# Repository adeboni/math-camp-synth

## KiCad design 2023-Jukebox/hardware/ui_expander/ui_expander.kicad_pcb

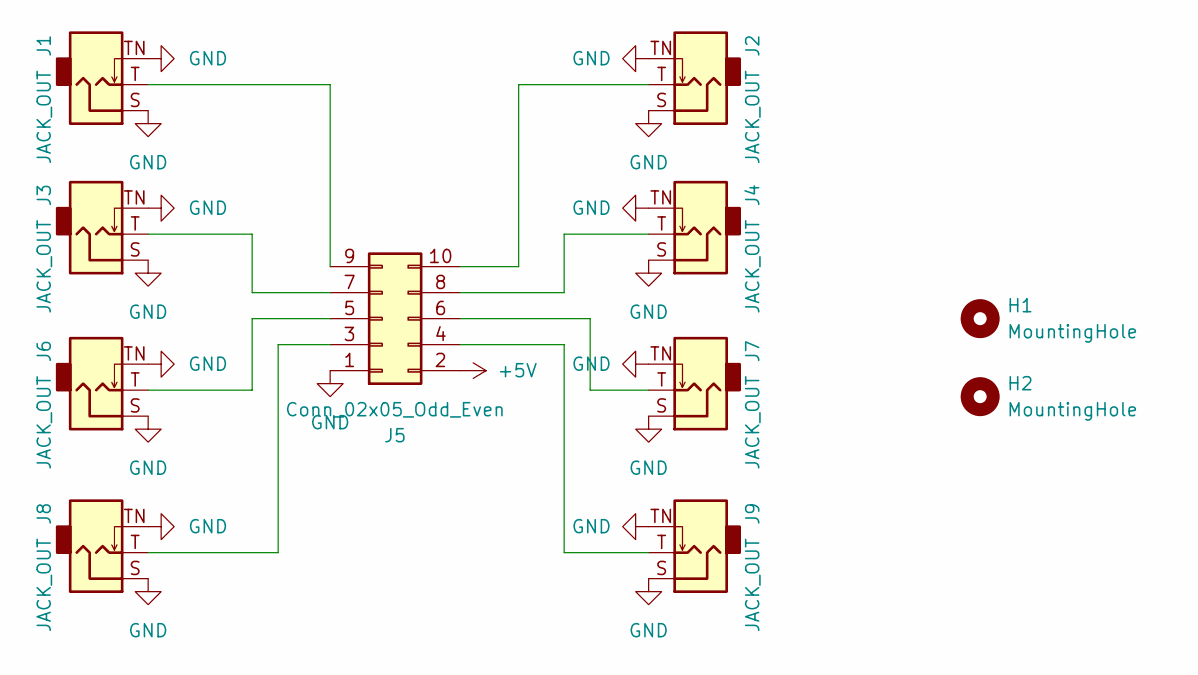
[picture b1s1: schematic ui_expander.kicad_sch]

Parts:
H1, H2: MountingHole; MountingHole_2.2mm_M2
J1, J2, J3, J4, J6, J7, J8, J9: JACK_OUT; Jack_3.5mm_QingPu_WQP-PJ398SM_Vertical_CircularHoles
J5: Conn_02x05_Odd_Even; IDC-Header_2x05_P2.54mm_Vertical

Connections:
+5V: J5.2
GND: J1.S, J1.TN, J2.S, J2.TN, J3.S, J3.TN, J4.S, J4.TN, J5.1, J6.S, J6.TN, J7.S, J7.TN, J8.S, J8.TN, J9.S, J9.TN
unnamed: J1.T, J5.9
unnamed: J2.T, J5.10
unnamed: J3.T, J5.7
unnamed: J4.T, J5.8
unnamed: J5.3, J8.T
unnamed: J5.4, J9.T
unnamed: J5.5, J6.T
unnamed: J5.6, J7.T

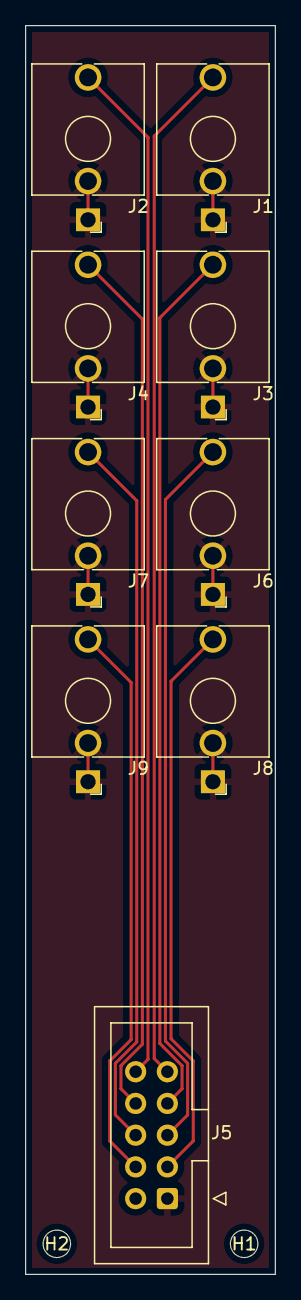
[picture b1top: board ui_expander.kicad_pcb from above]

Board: 2 copper layers, 20.0 x 100.0 mm, 11 parts (0 on the bottom side), 9 nets.

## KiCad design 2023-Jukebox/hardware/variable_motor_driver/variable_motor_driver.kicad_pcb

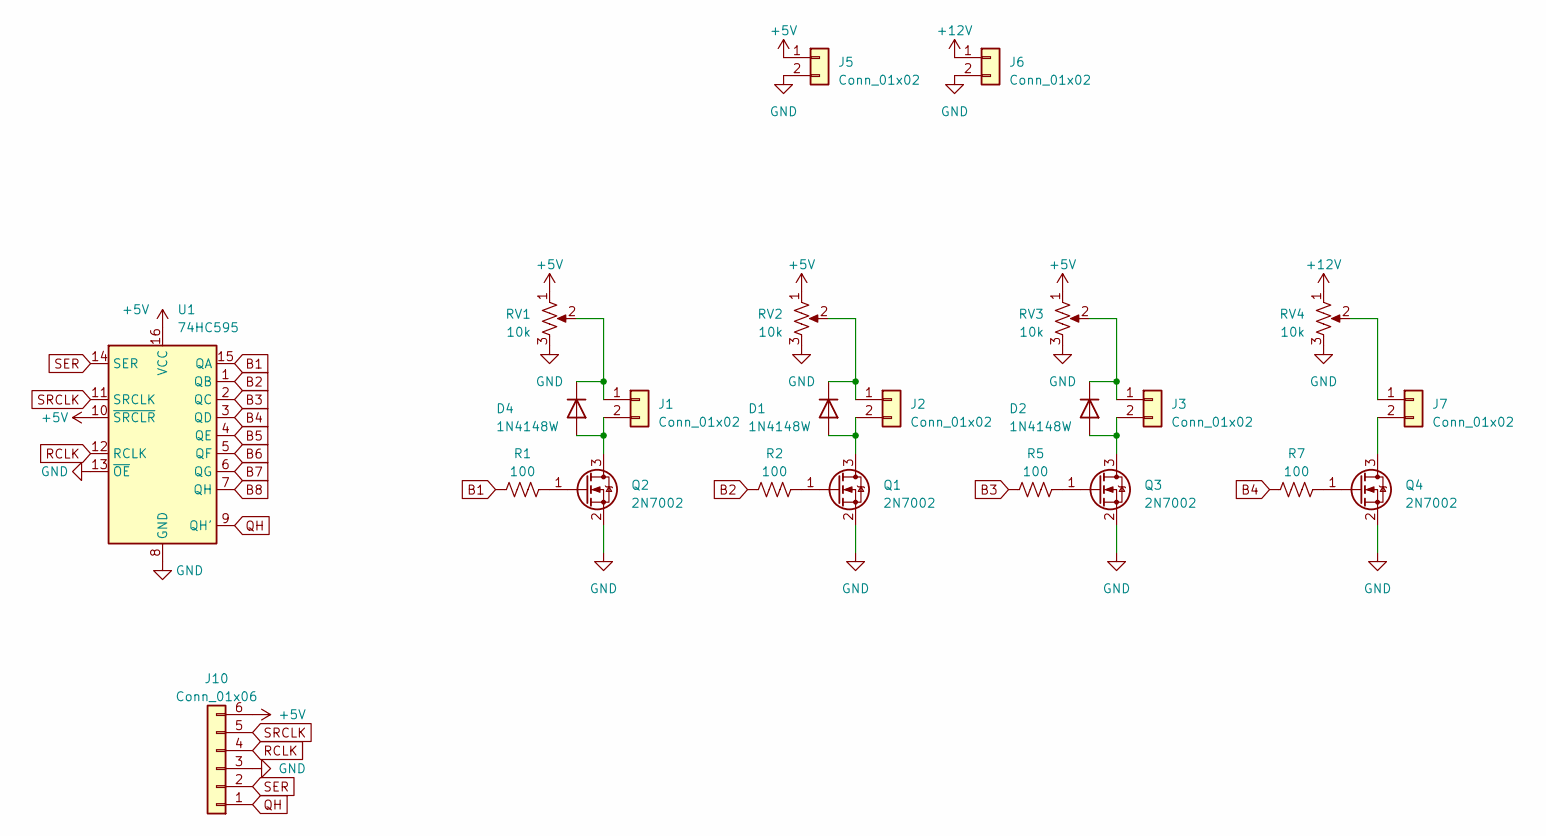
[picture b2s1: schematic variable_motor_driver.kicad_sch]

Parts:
D1, D2, D4: 1N4148W; D_SOD-123
J1, J2, J3, J5, J6, J7: Conn_01x02; JST_XH_B2B-XH-A_1x02_P2.50mm_Vertical
J10: Conn_01x06; PinSocket_1x06_P2.54mm_Vertical
Q1, Q2, Q3, Q4: 2N7002; SOT-23
R1, R2, R5, R7: 100; R_0603_1608Metric
RV1, RV2, RV3, RV4: 10k; Potentiometer_Bourns_3386P_Vertical
U1: 74HC595; SOIC-16_3.9x9.9mm_P1.27mm

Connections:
+5V: J5.1, RV1.1, RV2.1, RV3.1, U1.10 (~SRCLR), U1.16 (VCC); also elsewhere on the board
+12V: J6.1, RV4.1
B1: R1.1, U1.15 (QA)
B2: R2.1, U1.1 (QB)
B3: R5.1, U1.2 (QC)
B4: R7.1, U1.3 (QD)
B5: U1.4 (QE)
B6: U1.5 (QF)
B7: U1.6 (QG)
B8: U1.7 (QH)
GND: J5.2, J6.2, Q1.2 (S), Q2.2 (S), Q3.2 (S), Q4.2 (S), RV1.3, RV2.3, RV3.3, RV4.3, U1.8 (GND), U1.13 (~OE); also elsewhere on the board
unnamed: D1.2 (A), J2.2, Q1.3 (D)
unnamed: D1.1 (K), J2.1, RV2.2
unnamed: D2.2 (A), J3.2, Q3.3 (D)
unnamed: D2.1 (K), J3.1, RV3.2
unnamed: D4.2 (A), J1.2, Q2.3 (D)
unnamed: D4.1 (K), J1.1, RV1.2
unnamed: J7.1, RV4.2
unnamed: J7.2, Q4.3 (D)
unnamed: Q1.1 (G), R2.2
unnamed: Q2.1 (G), R1.2
unnamed: Q3.1 (G), R5.2
unnamed: Q4.1 (G), R7.2
QH: U1.9 (QH'); also elsewhere on the board
RCLK: U1.12 (RCLK); also elsewhere on the board
SER: U1.14 (SER); also elsewhere on the board
SRCLK: U1.11 (SRCLK); also elsewhere on the board

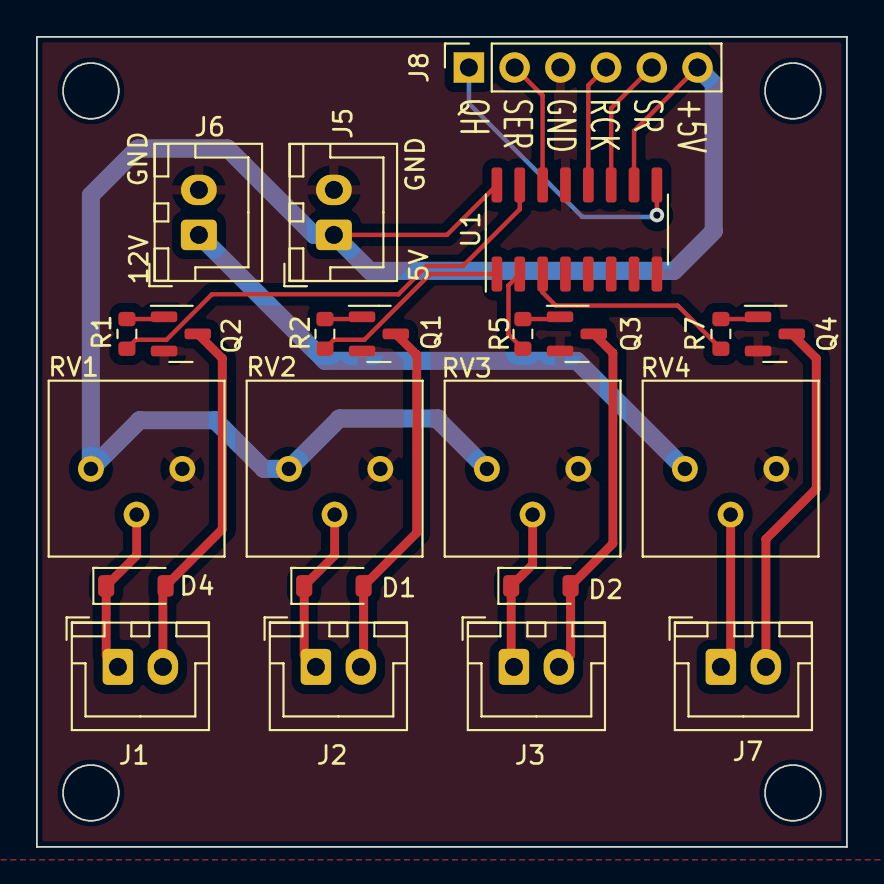
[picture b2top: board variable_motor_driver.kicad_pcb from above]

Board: 2 copper layers, 45.0 x 45.0 mm, 23 parts (0 on the bottom side), 23 nets.

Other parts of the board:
J8: Conn_01x06; PinSocket_1x06_P2.54mm_Vertical

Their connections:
+5V: J8.6; also elsewhere on the board
GND: J8.3; also elsewhere on the board
QH: J8.1; also elsewhere on the board
RCLK: J8.4; also elsewhere on the board
SER: J8.2; also elsewhere on the board
SRCLK: J8.5; also elsewhere on the board

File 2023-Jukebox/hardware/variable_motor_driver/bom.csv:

Comment,Designator,Footprint,LCSC Part Number
74HC595,U1,SOIC-16_3.9x9.9mm_P1.27mm,C5947
100,"R7,R5,R2,R1",R_0603_1608Metric,C22775
2N7002,"Q4,Q3,Q2,Q1",SOT-23,C8545
1N4148W,"D4,D2,D1",D_SOD-123,C81598

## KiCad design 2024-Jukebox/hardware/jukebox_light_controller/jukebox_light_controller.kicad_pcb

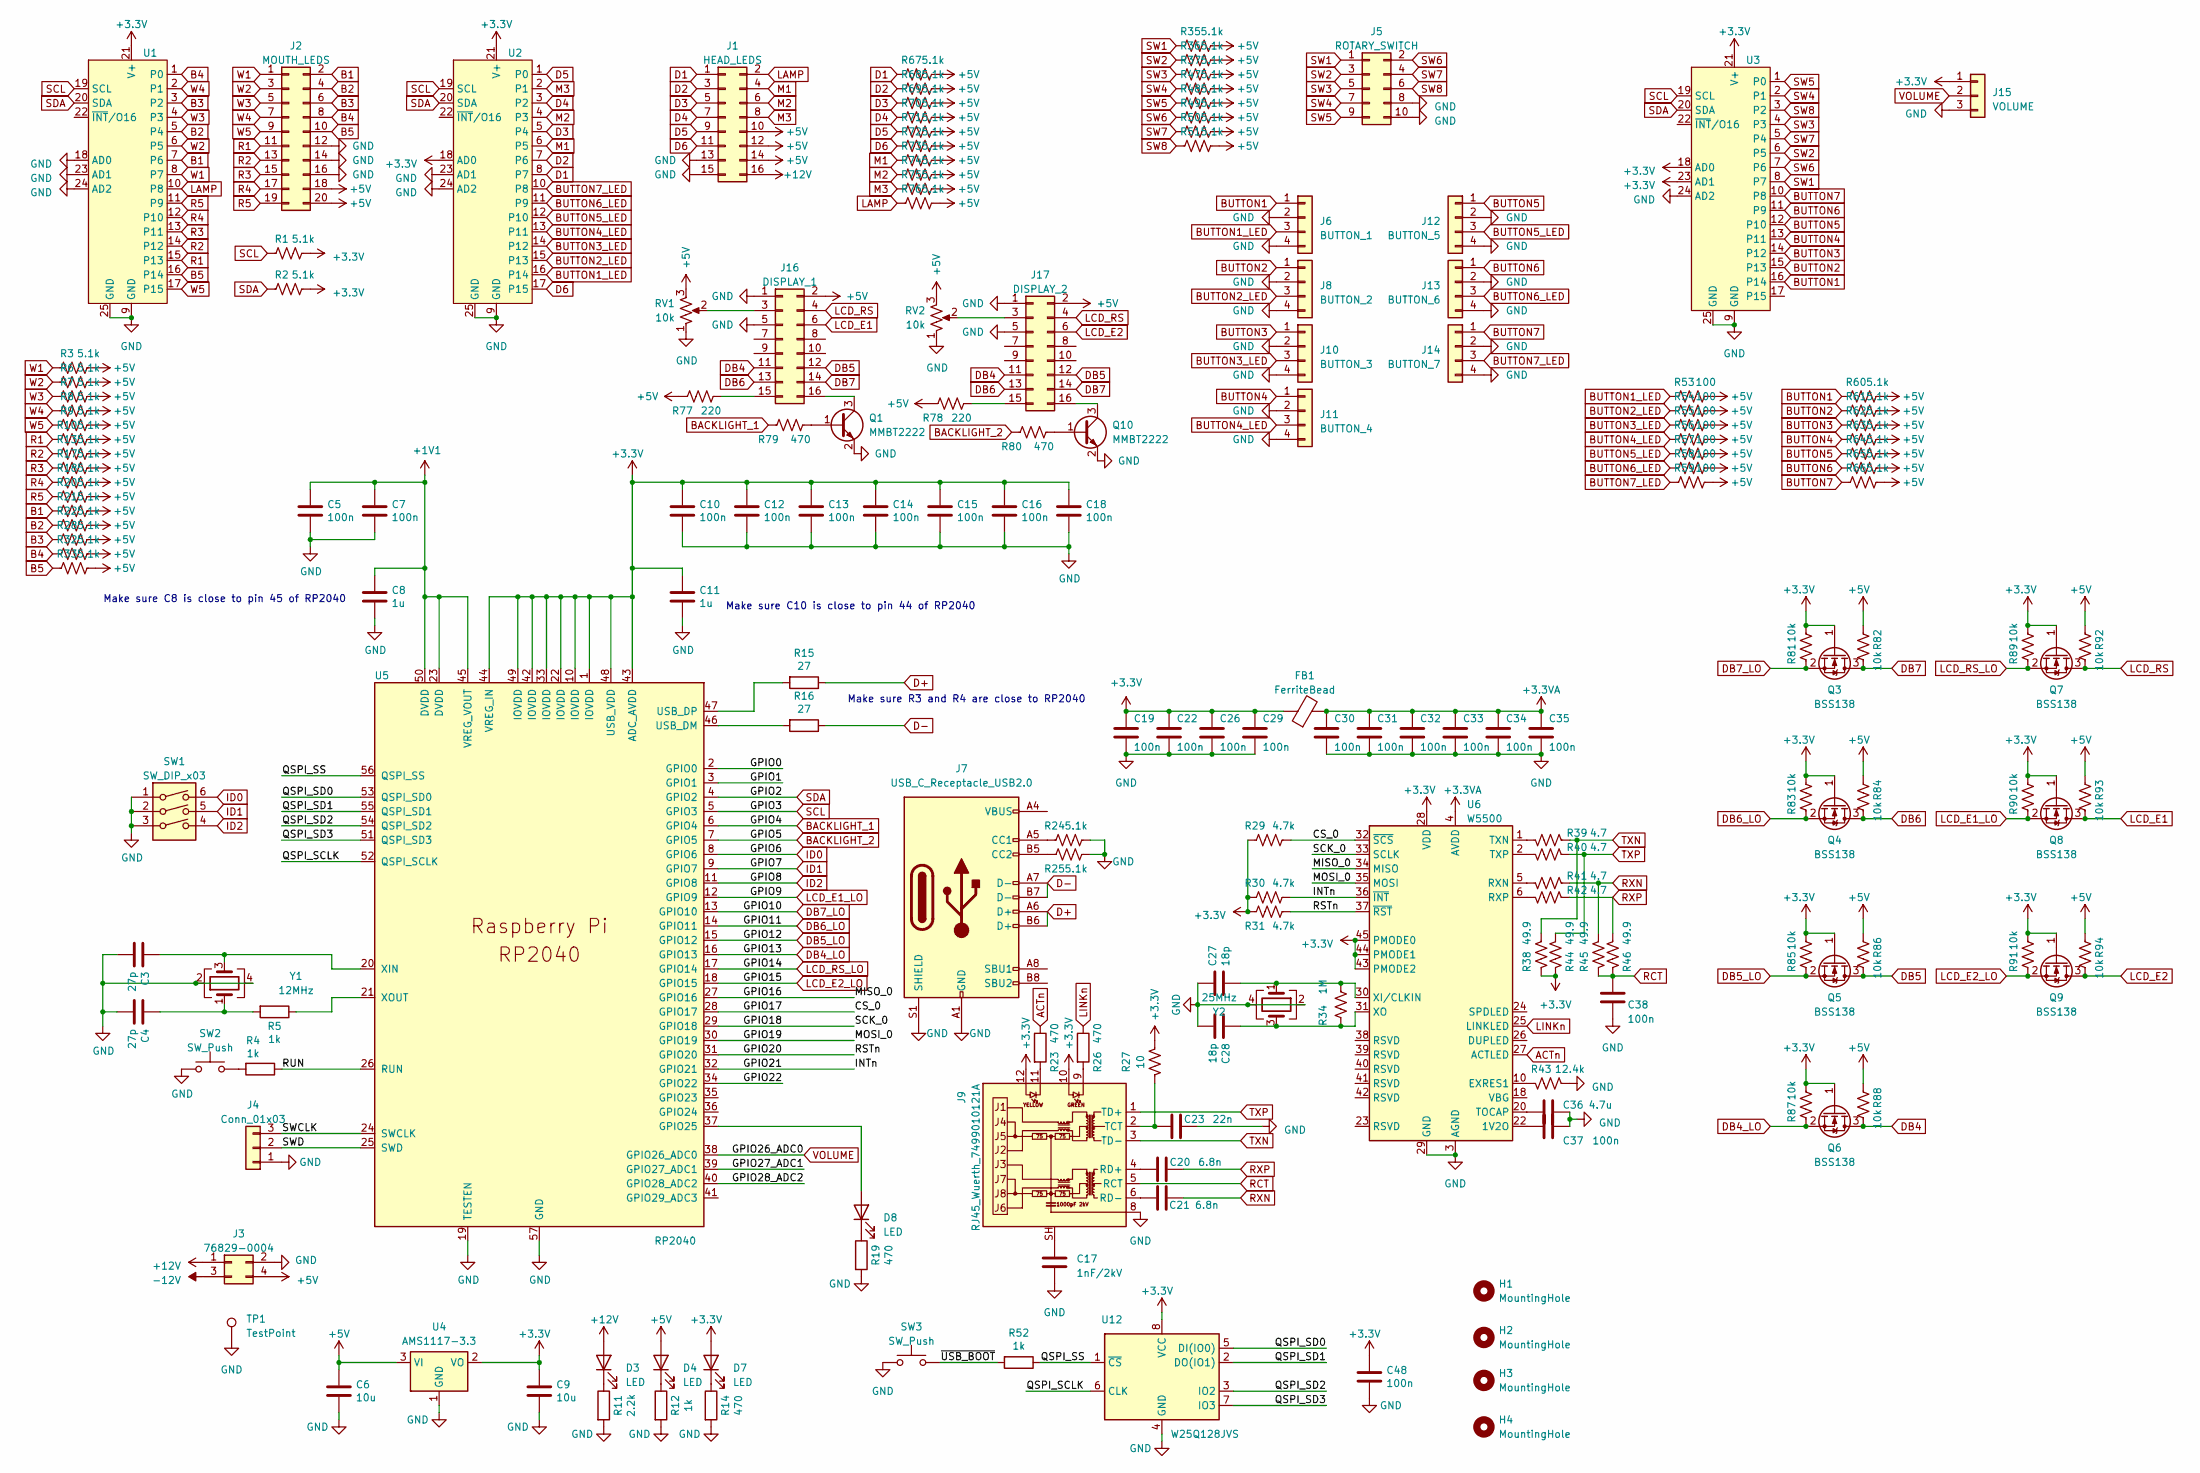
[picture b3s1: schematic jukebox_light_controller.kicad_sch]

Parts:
C3, C4: 27p; C_0603_1608Metric
C5, C7, C10, C12, C13, C14, C15, C16, C18, C19, C22, C26, C29, C30, C31, C32, C33, C34, C35, C37, C38, C48: 100n; C_0603_1608Metric
C6, C9: 10u; C_0603_1608Metric
C8, C11: 1u; C_0603_1608Metric
C17: 1nF/2kV; C_1206_3216Metric
C20, C21: 6.8n; C_0603_1608Metric
C23: 22n; C_0603_1608Metric
C27, C28: 18p; C_0603_1608Metric
C36: 4.7u; C_0603_1608Metric
D3, D4, D7, D8: LED; LED_0603_1608Metric
FB1: FerriteBead; L_0603_1608Metric
H1, H2, H3, H4: MountingHole; MountingHole_3.2mm_M3
J1: HEAD_LEDS; IDC-Header_2x08_P2.54mm_Vertical
J2: MOUTH_LEDS; IDC-Header_2x10_P2.54mm_Vertical
J3: 76829-0004; Molex_Mega-Fit_76829-0004_2x02_P5.70mm_Vertical
J4: Conn_01x03; PinHeader_1x03_P2.54mm_Vertical
J5: ROTARY_SWITCH; IDC-Header_2x05_P2.54mm_Vertical
J6: BUTTON_1; JST_XH_B4B-XH-A_1x04_P2.50mm_Vertical
J7: USB_C_Receptacle_USB2.0; USB_C_Receptacle_Palconn_UTC16-G
J8: BUTTON_2; JST_XH_B4B-XH-A_1x04_P2.50mm_Vertical
J9: RJ45_Wuerth_7499010121A; RJ45_Wuerth_7499010121A_Horizontal
J10: BUTTON_3; JST_XH_B4B-XH-A_1x04_P2.50mm_Vertical
J11: BUTTON_4; JST_XH_B4B-XH-A_1x04_P2.50mm_Vertical
J12: BUTTON_5; JST_XH_B4B-XH-A_1x04_P2.50mm_Vertical
J13: BUTTON_6; JST_XH_B4B-XH-A_1x04_P2.50mm_Vertical
J14: BUTTON_7; JST_XH_B4B-XH-A_1x04_P2.50mm_Vertical
J15: VOLUME; JST_XH_B3B-XH-A_1x03_P2.50mm_Vertical
J16: DISPLAY_1; IDC-Header_2x08_P2.54mm_Vertical
J17: DISPLAY_2; IDC-Header_2x08_P2.54mm_Vertical
Q1, Q10: MMBT2222; SOT-23
Q3, Q4, Q5, Q6, Q7, Q8, Q9: BSS138; SOT-23
R1, R2, R3, R6, R7, R8, R9, R10, R13, R17, R18, R20, R21, R22, R24, R25, R28, R32, R33, R35, R36, R37, R47, R48, R49, R50, R51, R60, R61, R62, R63, R64, R65, R66, R67, R68, R69, R70, R71, R72, R73, R74, R75, R76: 5.1k; R_0603_1608Metric
R4, R5, R12, R52: 1k; R_0603_1608Metric
R11: 2.2k; R_0603_1608Metric
R14, R19, R23, R26, R79, R80: 470; R_0603_1608Metric
R15, R16: 27; R_0603_1608Metric
R27: 10; R_0603_1608Metric
R29, R30, R31: 4.7k; R_0603_1608Metric
R34: 1M; R_0603_1608Metric
R38, R44, R45, R46: 49.9; R_0603_1608Metric
R39, R40, R41, R42: 4.7; R_0603_1608Metric
R43: 12.4k; R_0603_1608Metric
R53, R54, R55, R56, R57, R58, R59: 100; R_0603_1608Metric
R77, R78: 220; R_0603_1608Metric
R81, R82, R83, R84, R85, R86, R87, R88, R89, R90, R91, R92, R93, R94: 10k; R_0603_1608Metric
RV1, RV2: 10k; Potentiometer_Bourns_3386P_Vertical
SW1: SW_DIP_x03; SW_DIP_SPSTx03_Slide_9.78x9.8mm_W7.62mm_P2.54mm
SW2, SW3: SW_Push; SW_SPST_TL3342
TP1: TestPoint; TestPoint_Loop_D2.60mm_Drill1.4mm_Beaded
U1, U2, U3: TQFN-24-1EP_4x4mm_P0.5mm_EP2.6x2.6mm_ThermalVias
U4: AMS1117-3.3; SOT-223-3_TabPin2
U5: RP2040; QFN-56-1EP_7x7mm_P0.4mm_EP3.2x3.2mm
U6: W5500; LQFP-48_7x7mm_P0.5mm
U12: W25Q128JVS; SOIC-8_5.23x5.23mm_P1.27mm
Y1: 12MHz; Crystal_SMD_3225-4Pin_3.2x2.5mm
Y2: 25MHz; Crystal_SMD_3225-4Pin_3.2x2.5mm

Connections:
+1V1: C5.1, C7.1, C8.1, U5.23 (DVDD), U5.45 (VREG_VOUT), U5.50 (DVDD)
+3.3V: C9.1, C10.1, C11.1, C12.1, C13.1, C14.1, C15.1, C16.1, C18.1, C19.1, C22.1, C26.1, C29.1, C48.1, D7.2 (A), FB1.1, J9.10, J9.12, J15.1, Q3.1 (G), Q4.1 (G), Q5.1 (G), Q6.1 (G), Q7.1 (G), Q8.1 (G), Q9.1 (G), R1.2, R2.2, R27.2, R29.1, R30.1, R31.1, R38.2, R44.2, R81.2, R83.2, R85.2, R87.2, R89.2, R90.2, R91.2, U1.21 (V+), U2.18 (AD0), U2.21 (V+), U3.18 (AD0), U3.21 (V+), U3.23 (AD1), U4.2 (VO), U5.1 (IOVDD), U5.10 (IOVDD), U5.22 (IOVDD), U5.33 (IOVDD), U5.42 (IOVDD), U5.43 (ADC_AVDD), U5.44 (VREG_IN), U5.48 (USB_VDD), U5.49 (IOVDD), U6.28 (VDD), U6.43 (PMODE2), U6.44 (PMODE1), U6.45 (PMODE0), U12.8 (VCC)
+3.3VA: C30.1, C31.1, C32.1, C33.1, C34.1, C35.1, FB1.2, U6.4 (AVDD), U6.8 (AVDD), U6.11 (AVDD), U6.15 (AVDD), U6.17 (AVDD), U6.21 (AVDD)
+5V: C6.1, D4.2 (A), J1.10, J1.12, J1.14, J2.18, J2.20, J3.4, J16.2, J17.2, R3.2, R6.2, R7.2, R8.2, R9.2, R10.2, R13.2, R17.2, R18.2, R20.2, R21.2, R22.2, R28.2, R32.2, R33.2, R35.2, R36.2, R37.2, R47.2, R48.2, R49.2, R50.2, R51.2, R53.2, R54.2, R55.2, R56.2, R57.2, R58.2, R59.2, R60.2, R61.2, R62.2, R63.2, R64.2, R65.2, R66.2, R67.2, R68.2, R69.2, R70.2, R71.2, R72.2, R73.2, R74.2, R75.2, R76.2, R77.1, R78.1, R82.1, R84.1, R86.1, R88.1, R92.1, R93.1, R94.1, RV1.3, RV2.3, U4.3 (VI)
+12V: D3.2 (A), J1.16, J3.1
-12V: J3.3
/CS_0: R29.2, U5.28 (GPIO17), U6.32 (~SCS)
/GPIO0: U5.2 (GPIO0)
/GPIO1: U5.3 (GPIO1)
/GPIO16: U5.27 (GPIO16), U6.34 (MISO)
/GPIO18: U5.29 (GPIO18), U6.33 (SCLK)
/GPIO19: U5.30 (GPIO19), U6.35 (MOSI)
/GPIO20: R31.2, U5.31 (GPIO20), U6.37 (~RST)
/GPIO21: R30.2, U5.32 (GPIO21), U6.36 (~INT)
/GPIO22: U5.34 (GPIO22)
/GPIO27_ADC1: U5.39 (GPIO27_ADC1)
/GPIO28_ADC2: U5.40 (GPIO28_ADC2)
/QSPI_SCLK: U5.52 (QSPI_SCLK), U12.6 (CLK)
/QSPI_SD0: U5.53 (QSPI_SD0), U12.5 (DI(IO0))
/QSPI_SD1: U5.55 (QSPI_SD1), U12.2 (DO(IO1))
/QSPI_SD2: U5.54 (QSPI_SD2), U12.3 (IO2)
/QSPI_SD3: U5.51 (QSPI_SD3), U12.7 (IO3)
/QSPI_SS: R52.1, U5.56 (QSPI_SS), U12.1 (~CS)
/RUN: R4.1, U5.26 (RUN)
/SWCLK: J4.3, U5.24 (SWCLK)
/SWD: J4.2, U5.25 (SWD)
/~USB_BOOT: R52.2, SW3.2
ACTn: R23.1, U6.27 (ACTLED)
B1: J2.2, R21.1, U1.7 (P6)
B2: J2.4, R22.1, U1.5 (P4)
B3: J2.6, R28.1, U1.3 (P2)
B4: J2.8, R32.1, U1.1 (P0)
B5: J2.10, R33.1, U1.16 (P14)
BACKLIGHT_1: R79.1, U5.6 (GPIO4)
BACKLIGHT_2: R80.1, U5.7 (GPIO5)
BUTTON1: J6.1, R60.1, U3.16 (P14)
BUTTON1_LED: J6.3, R53.1, U2.16 (P14)
BUTTON2: J8.1, R61.1, U3.15 (P13)
BUTTON2_LED: J8.3, R54.1, U2.15 (P13)
BUTTON3: J10.1, R62.1, U3.14 (P12)
BUTTON3_LED: J10.3, R55.1, U2.14 (P12)
BUTTON4: J11.1, R63.1, U3.13 (P11)
BUTTON4_LED: J11.3, R56.1, U2.13 (P11)
BUTTON5: J12.1, R64.1, U3.12 (P10)
BUTTON5_LED: J12.3, R57.1, U2.12 (P10)
BUTTON6: J13.1, R65.1, U3.11 (P9)
BUTTON6_LED: J13.3, R58.1, U2.11 (P9)
BUTTON7: J14.1, R66.1, U3.10 (P8)
BUTTON7_LED: J14.3, R59.1, U2.10 (P8)
D1: J1.1, R67.1, U2.8 (P7)
D2: J1.3, R68.1, U2.7 (P6)
D3: J1.5, R69.1, U2.5 (P4)
D4: J1.7, R70.1, U2.3 (P2)
D5: J1.9, R71.1, U2.1 (P0)
D6: J1.11, R72.1, U2.17 (P15)
D+: J7.A6 (D+), J7.B6 (D+), R15.1
D-: J7.A7 (D-), J7.B7 (D-), R16.1
DB4: J16.11, J17.11, Q6.3 (D), R88.2
DB4_LO: Q6.2 (S), R87.1, U5.16 (GPIO13)
DB5: J16.12, J17.12, Q5.3 (D), R86.2
DB5_LO: Q5.2 (S), R85.1, U5.15 (GPIO12)
DB6: J16.13, J17.13, Q4.3 (D), R84.2
DB6_LO: Q4.2 (S), R83.1, U5.14 (GPIO11)
DB7: J16.14, J17.14, Q3.3 (D), R82.2
DB7_LO: Q3.2 (S), R81.1, U5.13 (GPIO10)
GND: C3.2, C4.2, C5.2, C6.2, C7.2, C8.2, C9.2, C10.2, C11.2, C12.2, C13.2, C14.2, C15.2, C16.2, C17.2, C18.2, C19.2, C22.2, C23.1, C26.2, C27.1, C28.2, C29.2, C30.2, C31.2, C32.2, C33.2, C34.2, C35.2, C36.2, C37.2, C38.1, C48.2, J1.13, J1.15, J2.12, J2.14, J2.16, J3.2, J4.1, J5.8, J5.10, J6.2, J6.4, J7.A1 (GND), J7.A12 (GND), J7.B1 (GND), J7.B12 (GND), J7.S1 (SHIELD), J8.2, J8.4, J9.8, J10.2, J10.4, J11.2, J11.4, J12.2, J12.4, J13.2, J13.4, J14.2, J14.4, J15.3, J16.1, J16.5, J17.1, J17.5, Q1.2 (E), Q10.2 (E), R11.2, R12.2, R14.2, R19.2, R24.1, R25.1, R43.1, RV1.1, RV2.1, SW1.1, SW1.2, SW1.3, SW2.1, SW3.1, TP1.1, U1.9 (GND), U1.18 (AD0), U1.23 (AD1), U1.24 (AD2), U1.25 (GND), U2.9 (GND), U2.23 (AD1), U2.24 (AD2), U2.25 (GND), U3.9 (GND), U3.24 (AD2), U3.25 (GND), U4.1 (GND), U5.19 (TESTEN), U5.57 (GND), U6.3 (AGND), U6.9 (AGND), U6.14 (AGND), U6.16 (AGND), U6.19 (AGND), U6.29 (GND), U6.48 (AGND), U12.4 (GND), Y1.2, Y1.4, Y2.2, Y2.4
ID0: SW1.6, U5.8 (GPIO6)
ID1: SW1.5, U5.9 (GPIO7)
ID2: SW1.4, U5.11 (GPIO8)
LAMP: J1.2, R76.1, U1.10 (P8)
LCD_E1: J16.6, Q8.3 (D), R93.2
LCD_E1_LO: Q8.2 (S), R90.1, U5.12 (GPIO9)
LCD_E2: J17.6, Q9.3 (D), R94.2
LCD_E2_LO: Q9.2 (S), R91.1, U5.18 (GPIO15)
LCD_RS: J16.4, J17.4, Q7.3 (D), R92.2
LCD_RS_LO: Q7.2 (S), R89.1, U5.17 (GPIO14)
LINKn: R26.1, U6.25 (LINKLED)
M1: J1.4, R73.1, U2.6 (P5)
M2: J1.6, R74.1, U2.4 (P3)
M3: J1.8, R75.1, U2.2 (P1)
unnamed: C4.1, R5.2, Y1.1
unnamed: C17.1, J9.SH
unnamed: D3.1 (K), R11.1
unnamed: D4.1 (K), R12.1
unnamed: D7.1 (K), R14.1
unnamed: D8.2 (A), U5.37 (GPIO25)
unnamed: D8.1 (K), R19.1
unnamed: J7.A5 (CC1), R24.2
unnamed: J7.B5 (CC2), R25.2
unnamed: J7.A4 (VBUS), J7.A9 (VBUS), J7.B4 (VBUS), J7.B9 (VBUS)
unnamed: J9.9, R26.2
unnamed: J9.11, R23.2
unnamed: C20.2, J9.4 (RD+)
unnamed: C21.1, J9.6 (RD-)
unnamed: C23.2, J9.2 (TCT), R27.1
unnamed: J16.3, RV1.2
unnamed: J16.15, R77.2
unnamed: J16.16, Q1.3 (C)
unnamed: J17.3, RV2.2
unnamed: J17.15, R78.2
unnamed: J17.16, Q10.3 (C)
unnamed: Q1.1 (B), R79.2
unnamed: Q10.1 (B), R80.2
unnamed: R4.2, SW2.2
unnamed: R16.2, U5.46 (USB_DM)
unnamed: R15.2, U5.47 (USB_DP)
unnamed: C3.1, U5.20 (XIN), Y1.3
unnamed: R5.1, U5.21 (XOUT)
unnamed: C37.1, U6.22 (1V2O)
unnamed: R43.2, U6.10 (EXRES1)
unnamed: R41.1, U6.5 (RXN)
unnamed: R42.2, U6.6 (RXP)
unnamed: C36.1, U6.20 (TOCAP)
unnamed: R39.1, U6.1 (TXN)
unnamed: R40.2, U6.2 (TXP)
unnamed: C27.2, R34.2, U6.30 (XI/CLKIN), Y2.1
unnamed: C28.1, R34.1, U6.31 (XO), Y2.3
R1: J2.11, R10.1, U1.15 (P13)
R2: J2.13, R13.1, U1.14 (P12)
R3: J2.15, R17.1, U1.13 (P11)
R4: J2.17, R18.1, U1.12 (P10)
R5: J2.19, R20.1, U1.11 (P9)
RCT: C38.2, J9.5 (RCT), R45.2, R46.2
RXN: C21.2, R41.2, R45.1
RXP: C20.1, R42.1, R46.1
SCL: R1.1, U1.19 (SCL), U2.19 (SCL), U3.19 (SCL), U5.5 (GPIO3)
SDA: R2.1, U1.20 (SDA), U2.20 (SDA), U3.20 (SDA), U5.4 (GPIO2)
SW1: J5.1, R35.1, U3.8 (P7)
SW2: J5.3, R36.1, U3.6 (P5)
SW3: J5.5, R37.1, U3.4 (P3)
SW4: J5.7, R47.1, U3.2 (P1)
SW5: J5.9, R48.1, U3.1 (P0)
SW6: J5.2, R49.1, U3.7 (P6)
SW7: J5.4, R50.1, U3.5 (P4)
SW8: J5.6, R51.1, U3.3 (P2)
TXN: J9.3 (TD-), R38.1, R39.2
TXP: J9.1 (TD+), R40.1, R44.1
VOLUME: J15.2, U5.38 (GPIO26_ADC0)
W1: J2.1, R3.1, U1.8 (P7)
W2: J2.3, R6.1, U1.6 (P5)
W3: J2.5, R7.1, U1.4 (P3)
W4: J2.7, R8.1, U1.2 (P1)
W5: J2.9, R9.1, U1.17 (P15)

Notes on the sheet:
Make sure R3 and R4 are close to RP2040
Make sure C10 is close to pin 44 of RP2040
Make sure C8 is close to pin 45 of RP2040

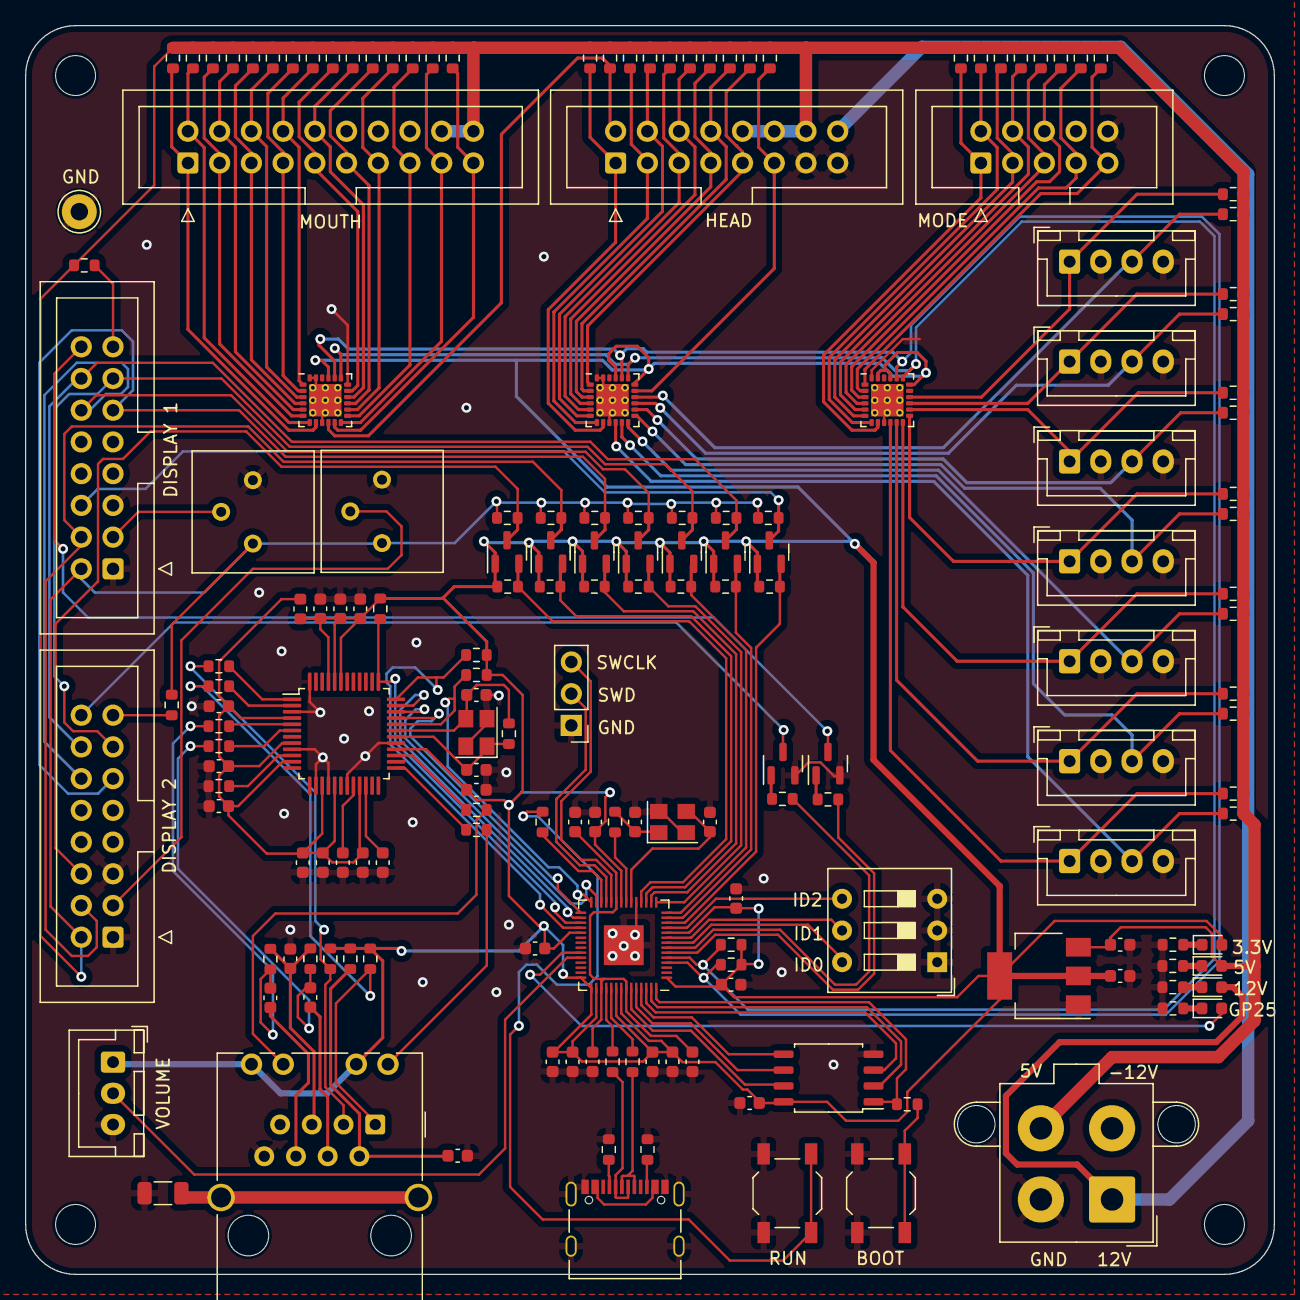
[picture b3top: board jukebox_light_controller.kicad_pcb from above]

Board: 2 copper layers, 100.0 x 100.0 mm, 179 parts (0 on the bottom side), 137 nets.

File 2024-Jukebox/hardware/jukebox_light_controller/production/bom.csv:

Designator,Footprint,Quantity,Value,LCSC Part #
"C10, C12, C13, C14, C15, C16, C18, C19, C22, C26, C29, C30, C31, C32, C33, C34, C35, C37, C38, C48, C5, C7",603,22,100n,C14663
"C11, C8",603,2,1u,C15849
"C20, C21",603,2,6.8n,C1631
C23,603,1,22n,C21122
"C27, C28",603,2,18p,C1647
"C3, C4",603,2,27p,C107045
C36,603,1,4.7u,C19666
"C6, C9",603,2,10u,C96446
"D3, D4, D7, D8",603,4,LED,C2286
FB1,603,1,FerriteBead,C1002
J7,USB_C_Receptacle_Palconn_UTC16-G,1,USB_C_Receptacle_USB2.0,C709357
"R1, R10, R13, R17, R18, R2, R20, R21, R22, R24, R25, R28, R3, R32, R33, R35, R36, R37, R47, R48, R49, R50, R51, R53, R54, R55, R56, R57, R58, R59, R6, R60, R61, R62, R63, R64, R65, R66, R67, R68, R69, R7, R70, R71, R72, R73, R74, R75, R76, R8, R9",603,51,5.1k,C23186
R11,603,1,2.2k,C4190
"R12, R4, R5, R52",603,4,1k,C21190
"R14, R19, R23, R26",603,4,470,C23179
"R15, R16",603,2,27,C25190
R27,603,1,10,C22859
"R29, R30, R31",603,3,4.7k,C23162
R34,603,1,1M,C22935
"R38, R44, R45, R46",603,4,49.9,C23185
"R39, R40, R41, R42",603,4,4.7,C23164
R43,603,1,12.4k,C22865
"R77, R78",603,2,220,C22962
"SW2, SW3",SW_SPST_TL3342,2,SW_Push,C318884
"U1, U2, U3",TQFN-24-1EP_4x4mm_P0.5mm_EP2.6x2.6mm_ThermalVias,3,MAX7313,C2669657
U12,SOIC-8_5.23x5.23mm_P1.27mm,1,W25Q128JVS,C97521
U4,SOT-223-3_TabPin2,1,AMS1117-3.3,C6186
U5,QFN-56-1EP_7x7mm_P0.4mm_EP3.2x3.2mm,1,RP2040,C2040
U6,LQFP-48_7x7mm_P0.5mm,1,W5500,C32843
Y1,Crystal_SMD_3225-4Pin_3.2x2.5mm,1,12MHz,C9002
Y2,Crystal_SMD_3225-4Pin_3.2x2.5mm,1,25MHz,C9006

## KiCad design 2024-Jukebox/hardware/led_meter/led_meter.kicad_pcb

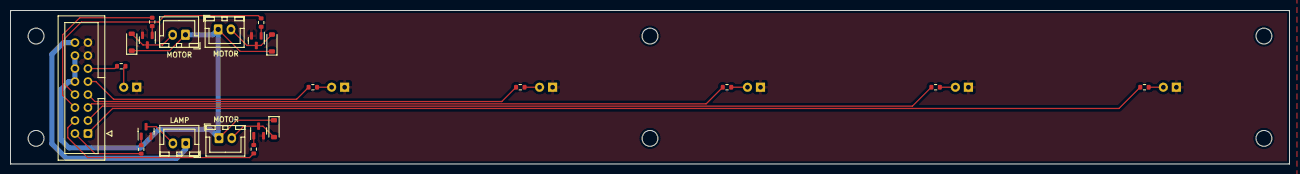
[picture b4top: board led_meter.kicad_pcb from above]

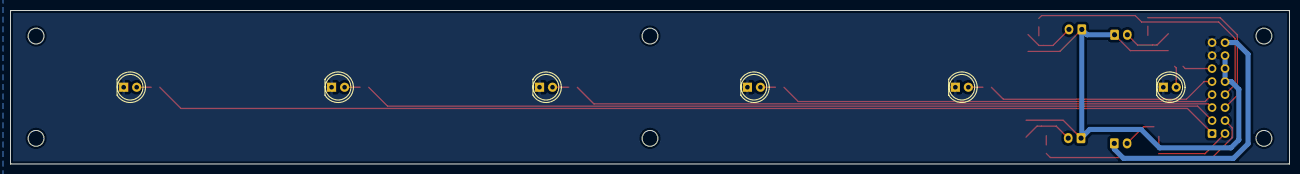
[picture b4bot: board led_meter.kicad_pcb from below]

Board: 2 copper layers, 250.0 x 30.0 mm, 28 parts (6 on the bottom side), 27 nets.

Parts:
D1, D2, D3, D4, D5, D6: LED; LED_D5.0mm_Clear
D7, D8, D9: 1N4148W; D_SOD-123
J1, J2, J3, J4: Conn_01x02; JST_XH_B2B-XH-A_1x02_P2.50mm_Vertical
J5: HEAD_LEDS; IDC-Header_2x08_P2.54mm_Vertical
Q1, Q2, Q3, Q4: 2N7002; SOT-23
R1, R2, R3, R4, R5, R6: 1k; R_0603_1608Metric
R7, R8, R9, R10: 100; R_0603_1608Metric

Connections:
+5V: D7.1 (K), D8.1 (K), D9.1 (K), J1.1, J2.1, J3.1, J5.10, J5.12, J5.14
+12V: J4.1, J5.16
D1: J5.1, R1.1
D2: J5.3, R2.1
D3: J5.5, R3.1
D4: J5.7, R4.1
D5: J5.9, R5.1
D6: J5.11, R6.1
GND: D1.1 (K), D2.1 (K), D3.1 (K), D4.1 (K), D5.1 (K), D6.1 (K), J5.13, J5.15, Q1.2 (S), Q2.2 (S), Q3.2 (S), Q4.2 (S)
LAMP: J5.2, R10.1
M1: J5.4, R7.1
M2: J5.6, R8.1
M3: J5.8, R9.1
unnamed: D1.2 (A), R1.2
unnamed: D2.2 (A), R2.2
unnamed: D3.2 (A), R3.2
unnamed: D4.2 (A), R4.2
unnamed: D5.2 (A), R5.2
unnamed: D6.2 (A), R6.2
unnamed: D7.2 (A), J1.2, Q1.3 (D)
unnamed: D8.2 (A), J2.2, Q2.3 (D)
unnamed: D9.2 (A), J3.2, Q3.3 (D)
unnamed: J4.2, Q4.3 (D)
unnamed: Q1.1 (G), R7.2
unnamed: Q2.1 (G), R8.2
unnamed: Q3.1 (G), R9.2
unnamed: Q4.1 (G), R10.2

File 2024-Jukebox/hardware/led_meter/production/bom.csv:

Designator,Footprint,Quantity,Value,LCSC Part #
"D7, D8, D9",D_SOD-123,3,1N4148W,C81598
"Q1, Q2, Q3, Q4",SOT-23,4,2N7002,C8545
"R1, R2, R3, R4, R5, R6",603,6,1k,C21190
"R10, R7, R8, R9",603,4,100,C22775
